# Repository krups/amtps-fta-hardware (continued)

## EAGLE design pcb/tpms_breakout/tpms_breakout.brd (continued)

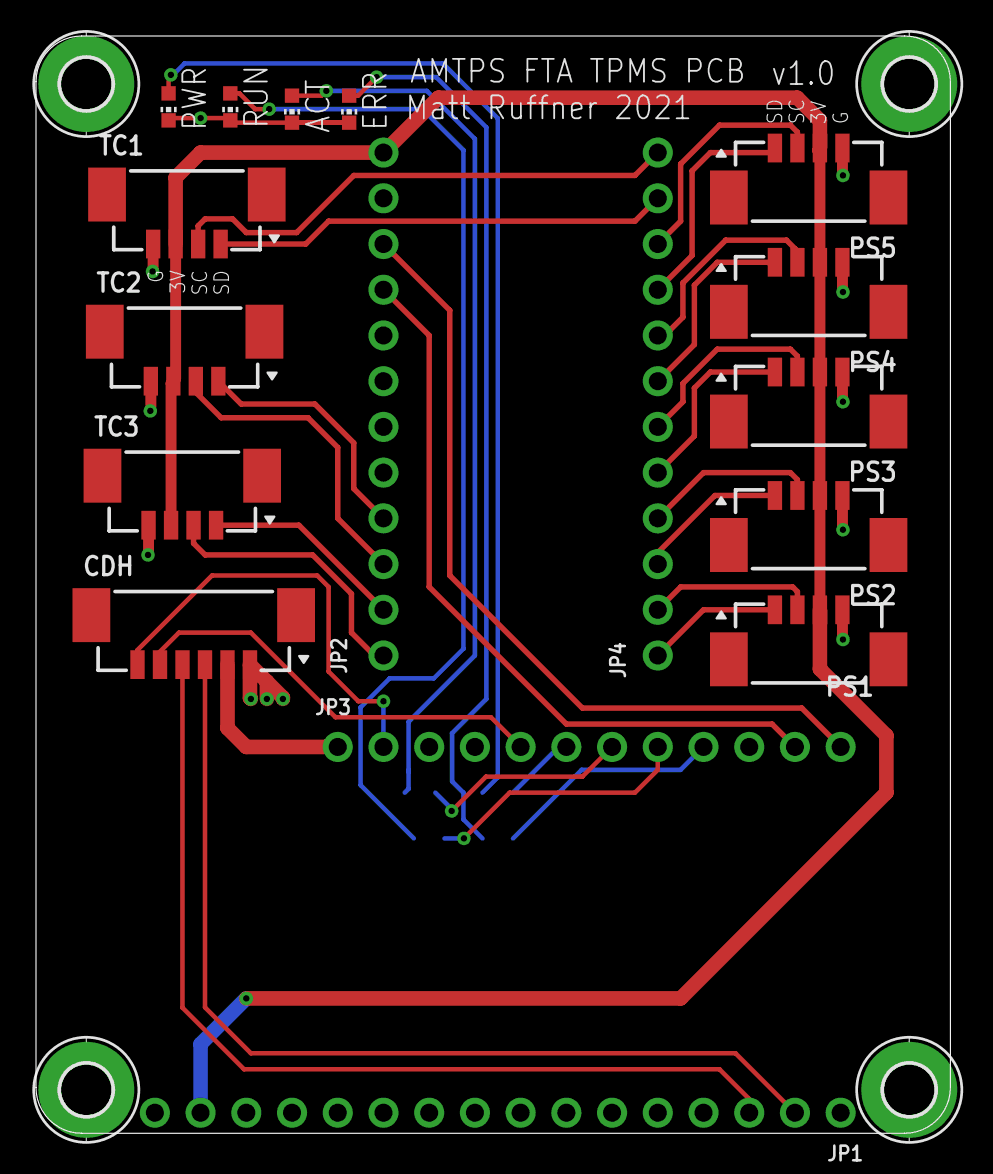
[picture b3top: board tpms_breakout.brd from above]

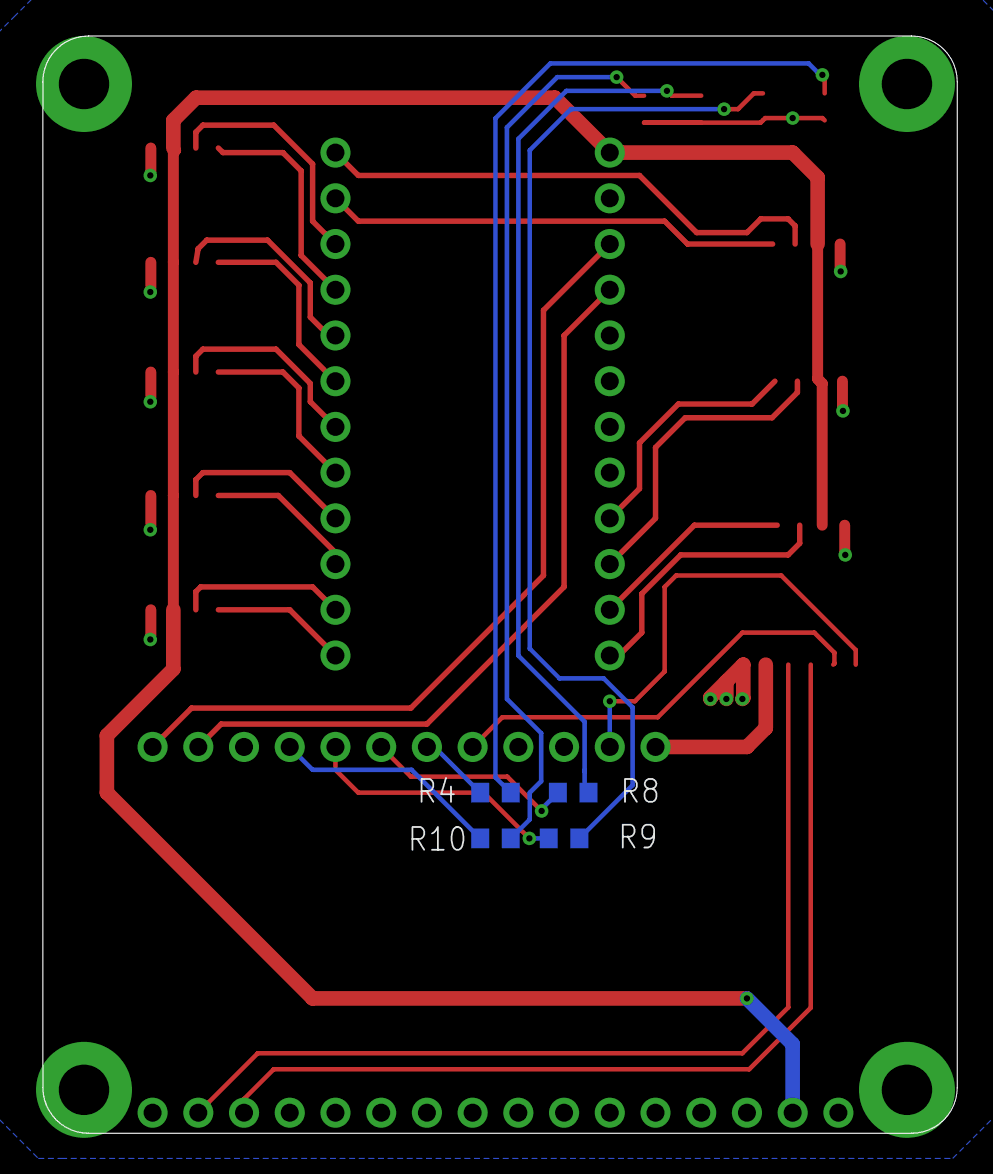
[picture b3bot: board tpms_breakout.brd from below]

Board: 2 copper layers, 50.8 x 61.0 mm, 25 parts (4 on the bottom side), 33 nets.

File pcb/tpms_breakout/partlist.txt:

Partlist

Exported from tpms_breakout.sch at 10/19/21 1:53 PM

EAGLE Version 9.6.2 Copyright (c) 1988-2020 Autodesk, Inc.

Assembly variant: 

Part     Value              Device             Package      Library             Sheet

ACT                         LEDCHIP-LED0603    CHIP-LED0603 adafruit            1
CDH      53398-0610         53398-0610         53398-0610   con-molex-picoblade 1
ERR                         LEDCHIP-LED0603    CHIP-LED0603 adafruit            1
H1       MOUNT-PAD-ROUND2.8 MOUNT-PAD-ROUND2.8 2,8-PAD      holes               1
H2       MOUNT-PAD-ROUND2.8 MOUNT-PAD-ROUND2.8 2,8-PAD      holes               1
H3       MOUNT-PAD-ROUND2.8 MOUNT-PAD-ROUND2.8 2,8-PAD      holes               1
H4       MOUNT-PAD-ROUND2.8 MOUNT-PAD-ROUND2.8 2,8-PAD      holes               1
JP1                         HEADER-1X16ROUND   1X16_ROUND   microbuilder        2
JP2                         HEADER-1X12        1X12_ROUND   microbuilder        2
JP3                         HEADER-1X12        1X12_ROUND   microbuilder        2
JP4                         HEADER-1X12        1X12_ROUND   microbuilder        2
PS1      53398-0410         53398-0410         53398-0410   con-molex-picoblade 1
PS2      53398-0410         53398-0410         53398-0410   con-molex-picoblade 1
PS3      53398-0410         53398-0410         53398-0410   con-molex-picoblade 1
PS4      53398-0410         53398-0410         53398-0410   con-molex-picoblade 1
PS5      53398-0410         53398-0410         53398-0410   con-molex-picoblade 1
PWR                         LEDCHIP-LED0603    CHIP-LED0603 adafruit            1
R4       470                R-US_R0603         R0603        rcl                 1
R8       470                R-US_R0603         R0603        rcl                 1
R9       470                R-US_R0603         R0603        rcl                 1
R10      470                R-US_R0603         R0603        rcl                 1
RUN                         LEDCHIP-LED0603    CHIP-LED0603 adafruit            1
TC1      53398-0410         53398-0410         53398-0410   con-molex-picoblade 1
TC2      53398-0410         53398-0410         53398-0410   con-molex-picoblade 1
TC3      53398-0410         53398-0410         53398-0410   con-molex-picoblade 1

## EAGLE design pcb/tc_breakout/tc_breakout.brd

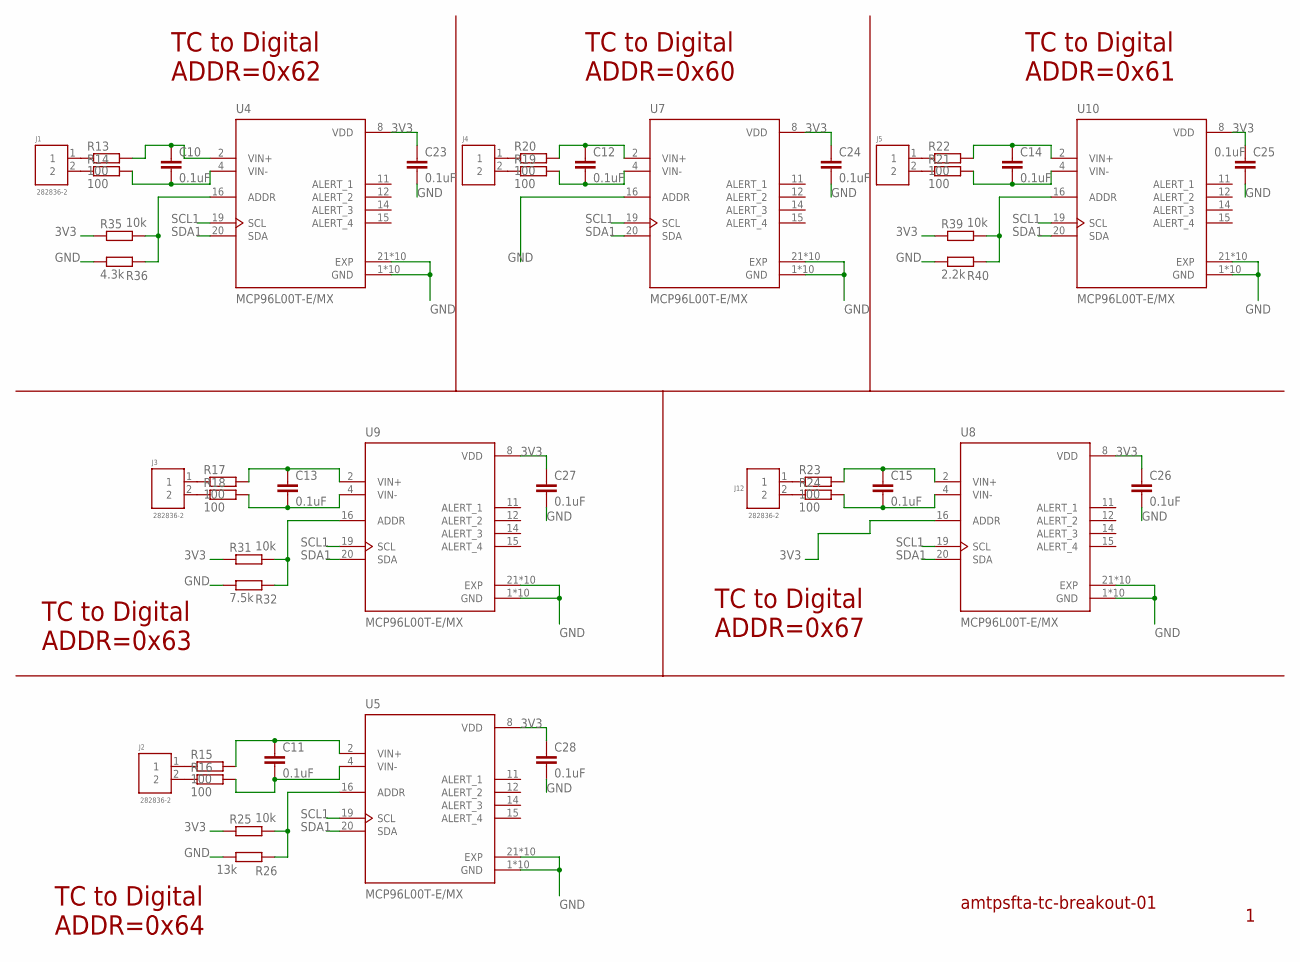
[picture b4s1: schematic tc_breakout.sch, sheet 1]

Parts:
C10, C11, C12, C13, C14, C15, C23, C24, C25, C26, C27, C28: 0.1uF; C0603
J1, J2, J3, J4, J5, J12: 282836-2; CONN_282836-2
R13, R14, R15, R16, R17, R18, R19, R20, R21, R22, R23, R24: 100; R0603
R25, R31, R35, R39: 10k; R0603
R26: 13k; R0603
R32: 7.5k; R0603
R36: 4.3k; R0603
R40: 2.2k; R0603
U4, U5, U7, U8, U9, U10: MCP96L00T-E/MX; QFN65P500X500X100-21N_MCP96L00T-E/MX

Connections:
3V3: C23.1, C24.1, C25.1, C26.1, C27.1, C28.1, R25.1, R31.1, R35.1, R39.1, U4.8 (VDD), U5.8 (VDD), U7.8 (VDD), U8.8 (VDD), U8.16 (ADDR), U9.8 (VDD), U10.8 (VDD); also elsewhere on the board
GND: C23.2, C24.2, C25.2, C26.2, C27.2, C28.2, R26.1, R32.1, R36.1, R40.1, U4.1 (GND), U4.3 (GND), U4.5 (GND), U4.6 (GND), U4.7 (GND), U4.9 (GND), U4.10 (GND), U4.13 (GND), U4.17 (GND), U4.18 (GND), U4.21 (EXP), U4.22 (EXP), U4.23 (EXP), U4.24 (EXP), U4.25 (EXP), U4.26 (EXP), U4.27 (EXP), U4.28 (EXP), U4.29 (EXP), U4.30 (EXP), U5.1 (GND), U5.3 (GND), U5.5 (GND), U5.6 (GND), U5.7 (GND), U5.9 (GND), U5.10 (GND), U5.13 (GND), U5.17 (GND), U5.18 (GND), U5.21 (EXP), U5.22 (EXP), U5.23 (EXP), U5.24 (EXP), U5.25 (EXP), U5.26 (EXP), U5.27 (EXP), U5.28 (EXP), U5.29 (EXP), U5.30 (EXP), U7.1 (GND), U7.3 (GND), U7.5 (GND), U7.6 (GND), U7.7 (GND), U7.9 (GND), U7.10 (GND), U7.13 (GND), U7.16 (ADDR), U7.17 (GND), U7.18 (GND), U7.21 (EXP), U7.22 (EXP), U7.23 (EXP), U7.24 (EXP), U7.25 (EXP), U7.26 (EXP), U7.27 (EXP), U7.28 (EXP), U7.29 (EXP), U7.30 (EXP), U8.1 (GND), U8.3 (GND), U8.5 (GND), U8.6 (GND), U8.7 (GND), U8.9 (GND), U8.10 (GND), U8.13 (GND), U8.17 (GND), U8.18 (GND), U8.21 (EXP), U8.22 (EXP), U8.23 (EXP), U8.24 (EXP), U8.25 (EXP), U8.26 (EXP), U8.27 (EXP), U8.28 (EXP), U8.29 (EXP), U8.30 (EXP), U9.1 (GND), U9.3 (GND), U9.5 (GND), U9.6 (GND), U9.7 (GND), U9.9 (GND), U9.10 (GND), U9.13 (GND), U9.17 (GND), U9.18 (GND), U9.21 (EXP), U9.22 (EXP), U9.23 (EXP), U9.24 (EXP), U9.25 (EXP), U9.26 (EXP), U9.27 (EXP), U9.28 (EXP), U9.29 (EXP), U9.30 (EXP), U10.1 (GND), U10.3 (GND), U10.5 (GND), U10.6 (GND), U10.7 (GND), U10.9 (GND), U10.10 (GND), U10.13 (GND), U10.17 (GND), U10.18 (GND), U10.21 (EXP), U10.22 (EXP), U10.23 (EXP), U10.24 (EXP), U10.25 (EXP), U10.26 (EXP), U10.27 (EXP), U10.28 (EXP), U10.29 (EXP), U10.30 (EXP); also elsewhere on the board
unnamed: J1.1, R13.1
unnamed: J1.2, R14.1
unnamed: J12.1, R23.1
unnamed: C10.1, R13.2, U4.2 (VIN+)
unnamed: C10.2, R14.2, U4.4 (VIN-)
unnamed: J2.1, R15.1
unnamed: J2.2, R16.1
unnamed: J3.1, R17.1
unnamed: J3.2, R18.1
unnamed: J4.2, R19.1
unnamed: J4.1, R20.1
unnamed: J5.2, R21.1
unnamed: J5.1, R22.1
unnamed: J12.2, R24.1
unnamed: C12.1, R20.2, U7.2 (VIN+)
unnamed: C12.2, R19.2, U7.4 (VIN-)
unnamed: C15.1, R23.2, U8.2 (VIN+)
unnamed: C14.2, R21.2, U10.4 (VIN-)
unnamed: C15.2, R24.2, U8.4 (VIN-)
unnamed: C14.1, R22.2, U10.2 (VIN+)
unnamed: C13.1, R17.2, U9.2 (VIN+)
unnamed: C13.2, R18.2, U9.4 (VIN-)
unnamed: C11.1, R15.2, U5.2 (VIN+)
unnamed: C11.2, R16.2, U5.4 (VIN-)
unnamed: R25.2, R26.2, U5.16 (ADDR)
unnamed: R31.2, R32.2, U9.16 (ADDR)
unnamed: R35.2, R36.2, U4.16 (ADDR)
unnamed: R39.2, R40.2, U10.16 (ADDR)
SCL1: U4.19 (SCL), U5.19 (SCL), U7.19 (SCL), U8.19 (SCL), U9.19 (SCL), U10.19 (SCL); also elsewhere on the board
SDA1: U4.20 (SDA), U5.20 (SDA), U7.20 (SDA), U8.20 (SDA), U9.20 (SDA), U10.20 (SDA); also elsewhere on the board

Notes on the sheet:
TC to Digital ADDR=0x60
TC to Digital ADDR=0x61
TC to Digital ADDR=0x62
TC to Digital ADDR=0x67
TC to Digital ADDR=0x63
TC to Digital ADDR=0x64
amtpsfta-tc-breakout-01

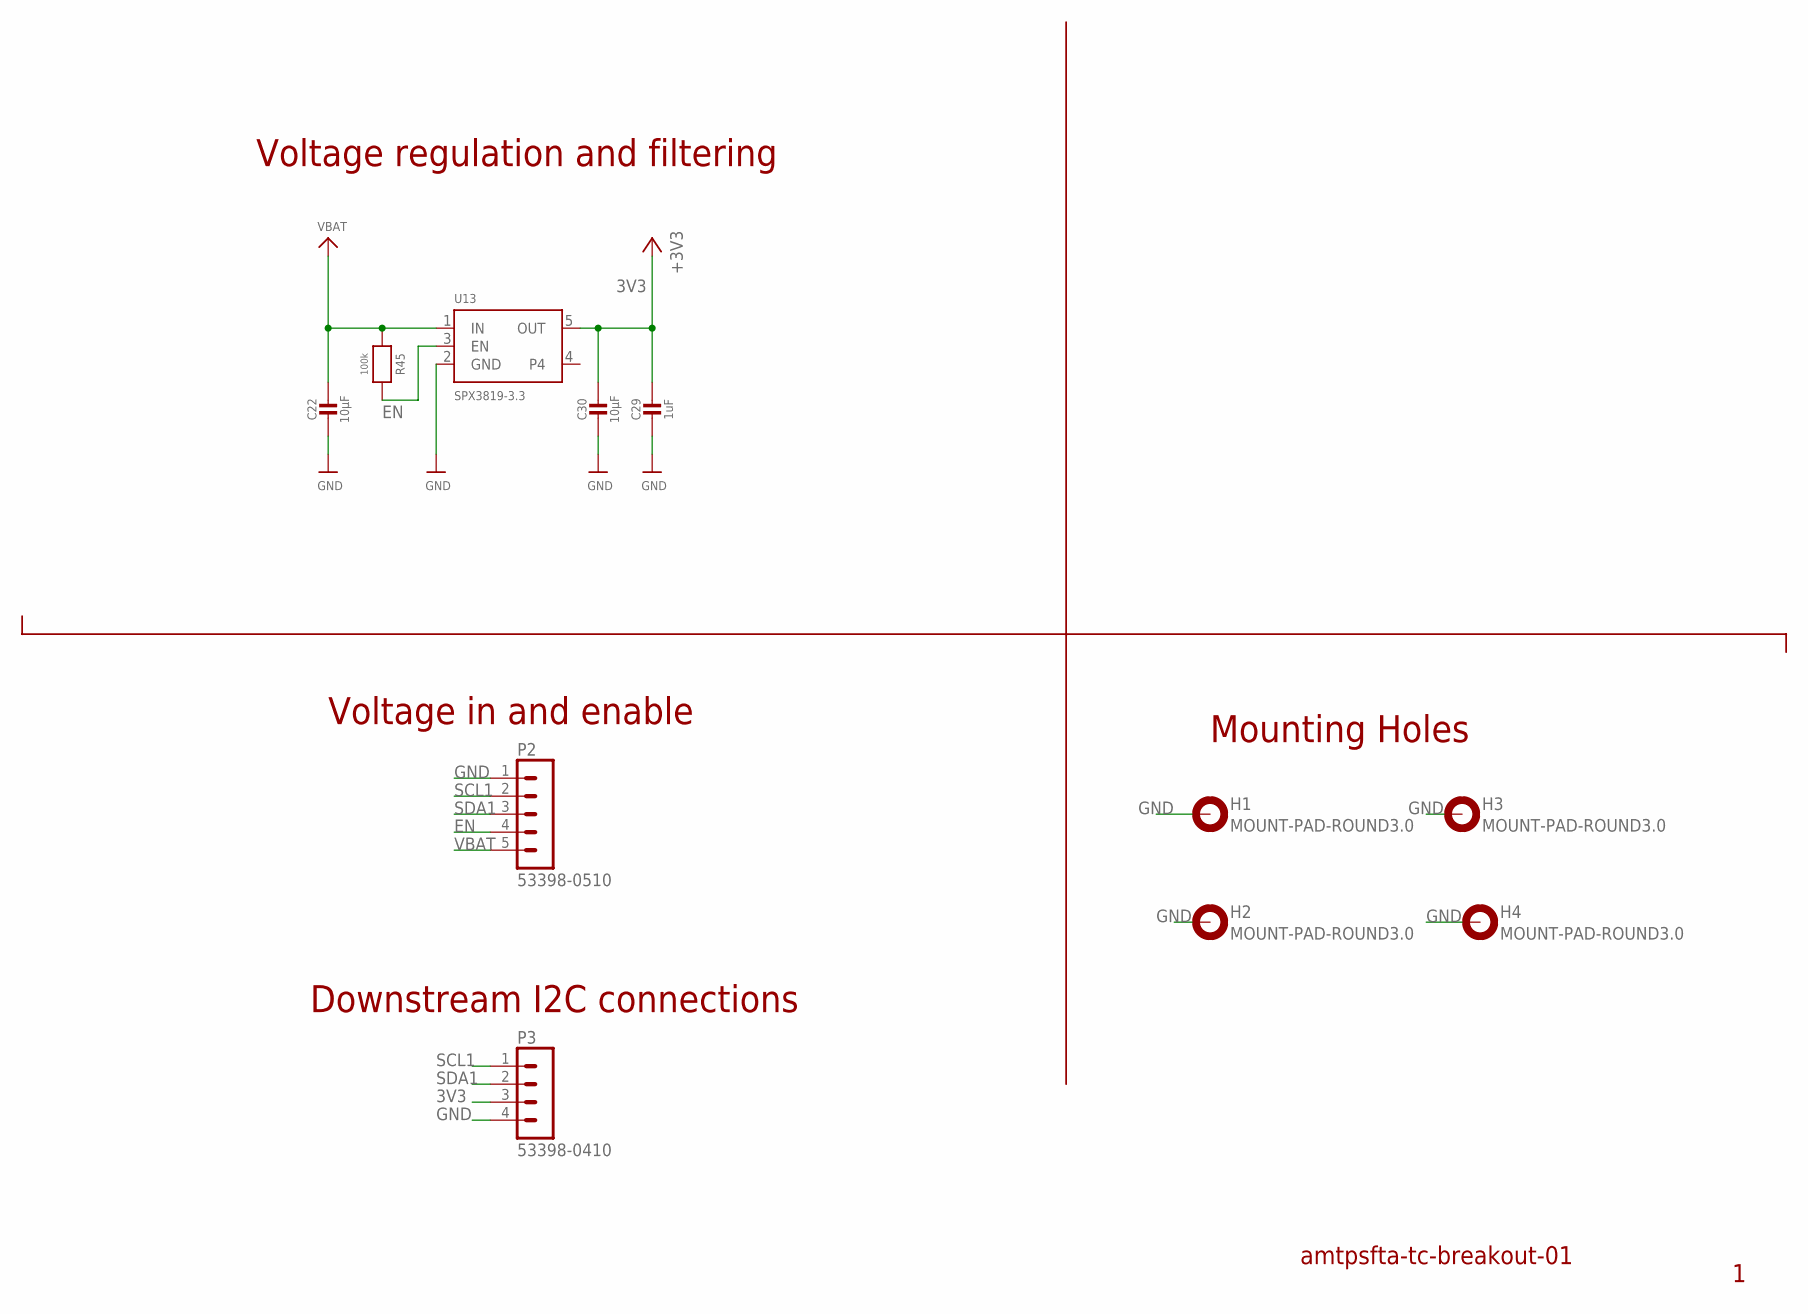
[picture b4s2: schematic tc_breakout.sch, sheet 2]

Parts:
C22, C30: 10µF; 0805-NO
C29: 1uF; 0603-NO
H1, H2, H3, H4: MOUNT-PAD-ROUND3.0; 3,0-PAD
P2: 53398-0510
P3: 53398-0410
R45: 100k; 0603-NO
U13: SPX3819-3.3; SOT23-5

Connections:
3V3: C29.1, C30.1, P3.3, U13.5 (OUT); also elsewhere on the board
EN: P2.4, R45.2, U13.3 (EN)
GND: C22.2, C29.2, C30.2, H1.B3,0, H2.B3,0, H3.B3,0, H4.B3,0, P2.1, P3.4, U13.2 (GND); also elsewhere on the board
SCL1: P2.2, P3.1; also elsewhere on the board
SDA1: P2.3, P3.2; also elsewhere on the board
VBAT: C22.1, P2.5, R45.1, U13.1 (IN)

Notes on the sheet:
Mounting Holes
Voltage in and enable
Downstream I2C connections
Voltage regulation and filtering
amtpsfta-tc-breakout-01

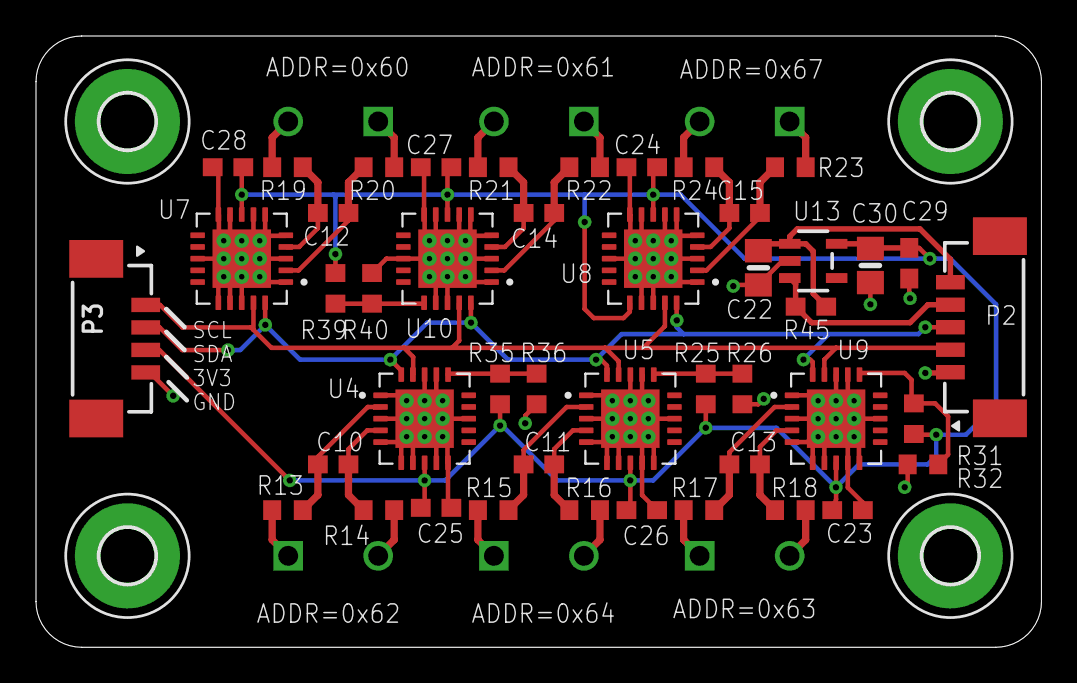
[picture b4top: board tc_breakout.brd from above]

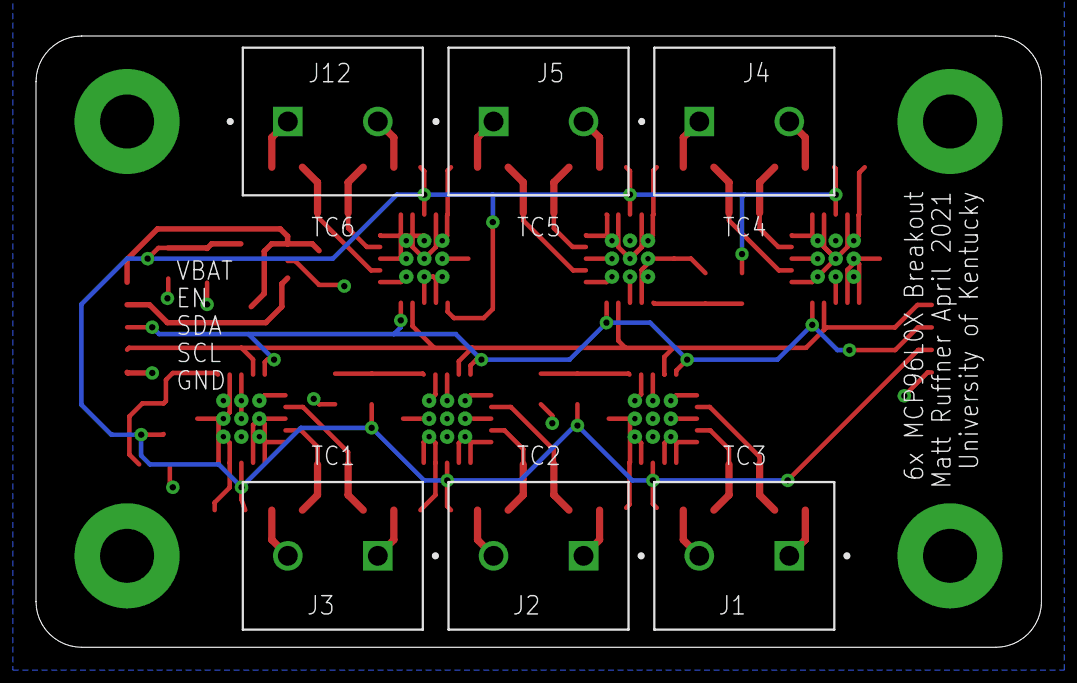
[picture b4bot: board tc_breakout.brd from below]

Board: 2 copper layers, 55.9 x 34.0 mm, 55 parts (6 on the bottom side), 34 nets.

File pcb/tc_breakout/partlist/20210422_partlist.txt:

Partlist

Exported from tc_breakout.brd at 4/22/21 8:15 AM

EAGLE Version 9.6.2 Copyright (c) 1988-2020 Autodesk, Inc.

Assembly variant: 

Part     Value              Package                              Library             Position (mil)        Orientation

C10      0.1uF              C0603                                rcl                 (650 400)             R0
C11      0.1uF              C0603                                rcl                 (1100 400)            R0
C12      0.1uF              C0603                                rcl                 (650 950)             R180
C13      0.1uF              C0603                                rcl                 (1550 400)            R0
C14      0.1uF              C0603                                rcl                 (1100 950)            R180
C15      0.1uF              C0603                                rcl                 (1550 950)            R180
C22      10µF               0805-NO                              microbuilder        (1580 830)            R270
C23      0.1uF              C0603                                rcl                 (1775 300)            R0
C24      0.1uF              C0603                                rcl                 (1325 1050)           R180
C25      0.1uF              C0603                                rcl                 (875 305)             R0
C26      0.1uF              C0603                                rcl                 (1325 300)            R0
C27      0.1uF              C0603                                rcl                 (875 1050)            R180
C28      0.1uF              C0603                                rcl                 (420 1050)            R180
C29      1uF                0603-NO                              microbuilder        (1910 840)            R270
C30      10µF               0805-NO                              microbuilder        (1825 835)            R270
H1       MOUNT-PAD-ROUND3.0 3,0-PAD                              holes               (200 200)             R0
H2       MOUNT-PAD-ROUND3.0 3,0-PAD                              holes               (2000 200)            R0
H3       MOUNT-PAD-ROUND3.0 3,0-PAD                              holes               (200 1150)            R0
H4       MOUNT-PAD-ROUND3.0 3,0-PAD                              holes               (2000 1150)           R0
J1       282836-2           CONN_282836-2                        282836-2            (650 200)             MR180
J2       282836-2           CONN_282836-2                        282836-2            (1100 200)            MR180
J3       282836-2           CONN_282836-2                        282836-2            (1550 200)            MR180
J4       282836-2           CONN_282836-2                        282836-2            (650 1150)            MR0
J5       282836-2           CONN_282836-2                        282836-2            (1100 1150)           MR0
J12      282836-2           CONN_282836-2                        282836-2            (1550 1150)           MR0
P2       53398-0510         53398-0510                           con-molex-picoblade (2000 700)            R270
R13      100                R0603                                rcl                 (550 300)             R0
R14      100                R0603                                rcl                 (750 300)             R180
R15      100                R0603                                rcl                 (1000 300)            R0
R16      100                R0603                                rcl                 (1200 300)            R180
R17      100                R0603                                rcl                 (1450 300)            R0
R18      100                R0603                                rcl                 (1650 300)            R180
R19      100                R0603                                rcl                 (550 1050)            R0
R20      100                R0603                                rcl                 (750 1050)            R180
R21      100                R0603                                rcl                 (1000 1050)           R0
R22      100                R0603                                rcl                 (1200 1050)           R180
R23      100                R0603                                rcl                 (1650 1050)           R180
R24      100                R0603                                rcl                 (1450 1050)           R0
R25      10k                R0603                                rcl                 (1465 565)            R90
R26      7.87k              R0603                                rcl                 (1545 565)            R90
R31      10k                R0603                                rcl                 (1920 500)            R90
R32      4.3k               R0603                                rcl                 (1940 400)            R0
R35      10k                R0603                                rcl                 (1015 565)            R90
R36      4.3k               R0603                                rcl                 (1095 565)            R90
R39      10k                R0603                                rcl                 (655 785)             R270
R40      2.2k               R0603                                rcl                 (735 785)             R270
R45      100k               0603-NO                              microbuilder        (1695 745)            R180
U4       MCP96L00T-E/MX     QFN65P500X500X100-21N_MCP96L00T-E/MX MCP96L00T-E_MX      (850 500)             R0
U5       MCP96L00T-E/MX     QFN65P500X500X100-21N_MCP96L00T-E/MX MCP96L00T-E_MX      (1300 500)            R0
U7       MCP96L00T-E/MX     QFN65P500X500X100-21N_MCP96L00T-E/MX MCP96L00T-E_MX      (450 850)             R180
U8       MCP96L00T-E/MX     QFN65P500X500X100-21N_MCP96L00T-E/MX MCP96L00T-E_MX      (1350 850)            R180
U9       MCP96L00T-E/MX     QFN65P500X500X100-21N_MCP96L00T-E/MX MCP96L00T-E_MX      (1750 500)            R0
U10      MCP96L00T-E/MX     QFN65P500X500X100-21N_MCP96L00T-E/MX MCP96L00T-E_MX      (900 850)             R180
U13      SPX3819-3.3        SOT23-5                              microbuilder        (1700 845)            R270

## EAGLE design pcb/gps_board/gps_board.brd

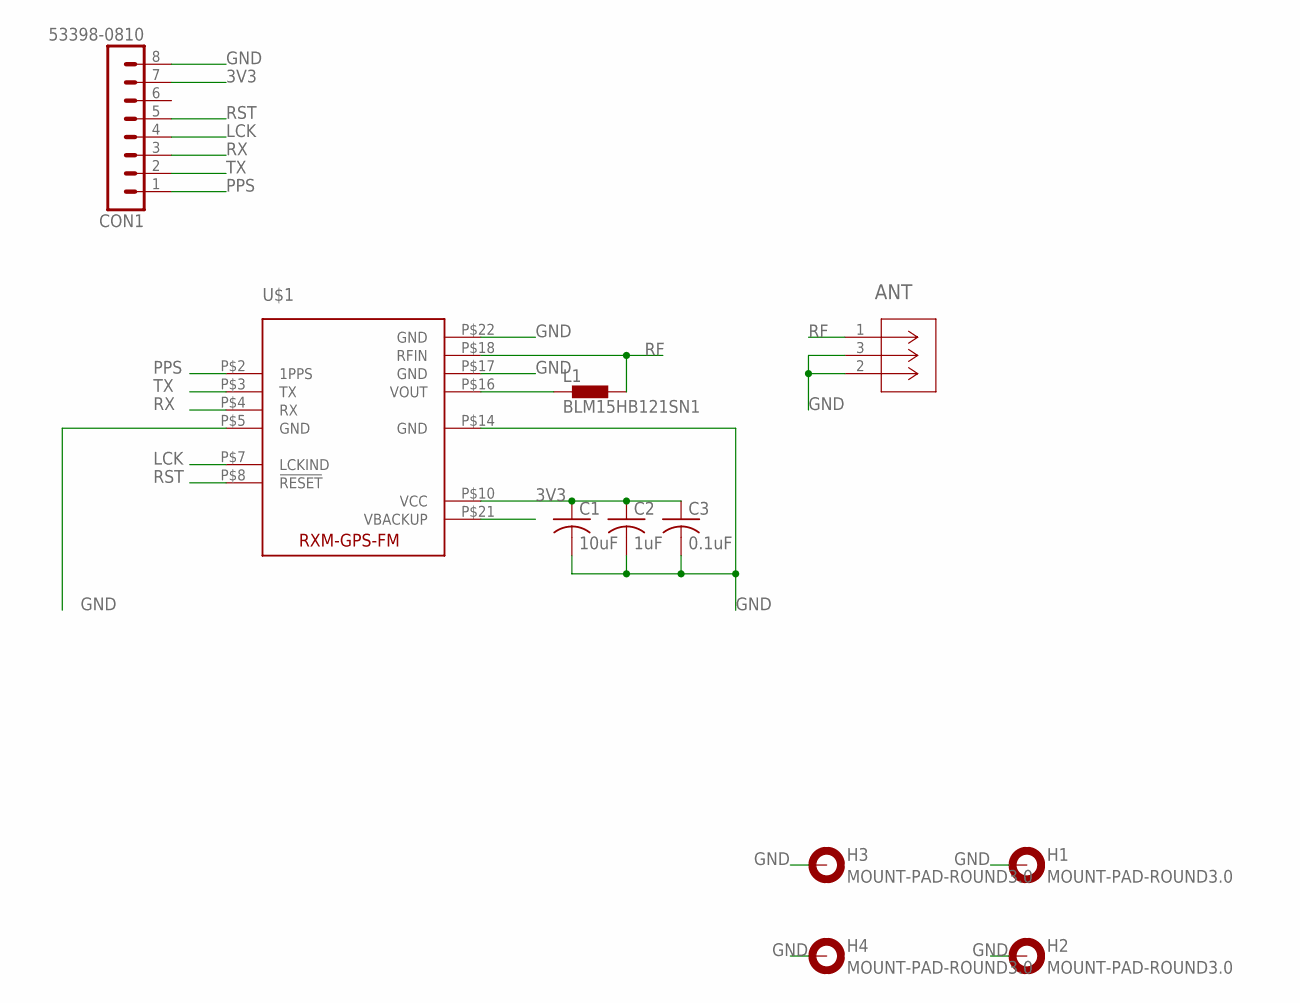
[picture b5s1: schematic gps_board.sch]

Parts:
ANT: U.FL-R-SMT-1(10); CONN_R-SMT-1(10)
C1: 10uF; C0603
C2: 1uF; C0603
C3: 0.1uF; C0603
CON1: 53398-0810
H1, H2, H3, H4: MOUNT-PAD-ROUND3.0; 3,0-PAD
L1: BLM15HB121SN1; 0402
U$1: RXM-GPS-FM

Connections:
3V3: C1.1, C2.1, C3.1, CON1.7, U$1.P$10 (VCC)
GND: ANT.2, ANT.3, C1.2, C2.2, C3.2, CON1.8, H1.B3,0, H2.B3,0, H3.B3,0, H4.B3,0, U$1.P$5 (GND), U$1.P$14 (GND), U$1.P$17 (GND), U$1.P$22 (GND)
LCK: CON1.4, U$1.P$7 (LCKIND)
unnamed: L1.1, U$1.P$16 (VOUT)
PPS: CON1.1, U$1.P$2 (1PPS)
RF: ANT.1, L1.2, U$1.P$18 (RFIN)
RST: CON1.5, U$1.P$8 (!RESET)
RX: CON1.3, U$1.P$4 (RX)
TX: CON1.2, U$1.P$3 (TX)

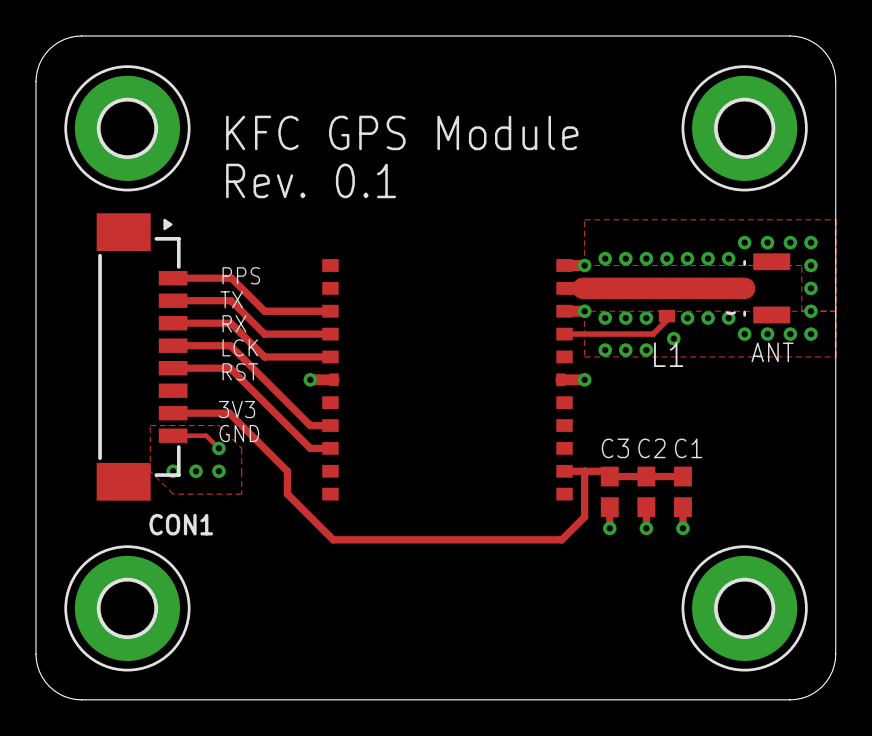
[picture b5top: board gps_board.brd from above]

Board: 2 copper layers, 44.4 x 36.9 mm, 11 parts (0 on the bottom side), 9 nets.

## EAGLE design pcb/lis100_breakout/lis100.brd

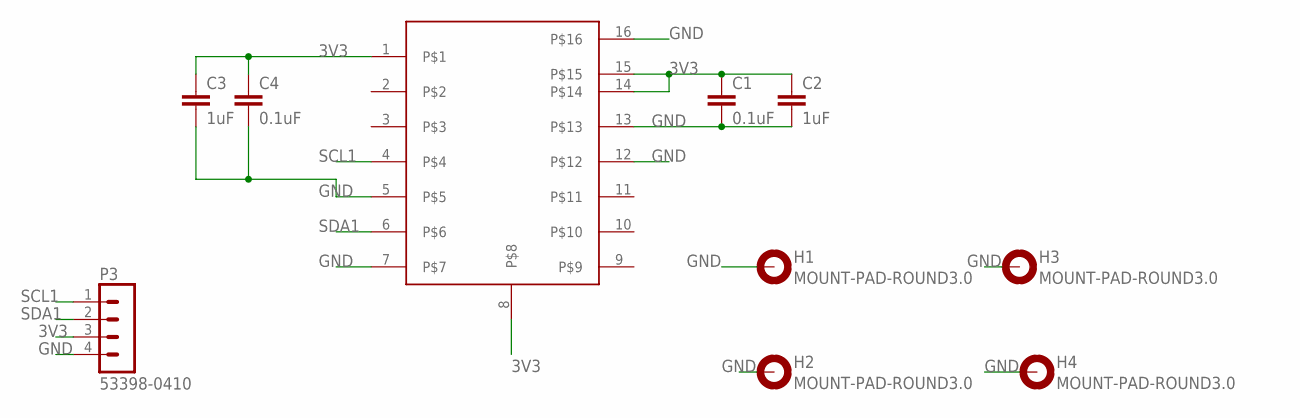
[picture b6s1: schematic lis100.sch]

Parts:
C1, C4: 0.1uF; C0603
C2, C3: 1uF; C0603
H1, H2, H3, H4: MOUNT-PAD-ROUND3.0; 3,0-PAD
P3: 53398-0410
U$1: H3LIS100DL; XDCR_LIS3DHTR

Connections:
3V3: C1.1, C2.1, C3.1, C4.1, P3.3, U$1.1, U$1.8, U$1.14, U$1.15
GND: C1.2, C2.2, C3.2, C4.2, H1.B3,0, H2.B3,0, H3.B3,0, H4.B3,0, P3.4, U$1.5, U$1.7, U$1.12, U$1.13, U$1.16
SCL1: P3.1, U$1.4
SDA1: P3.2, U$1.6

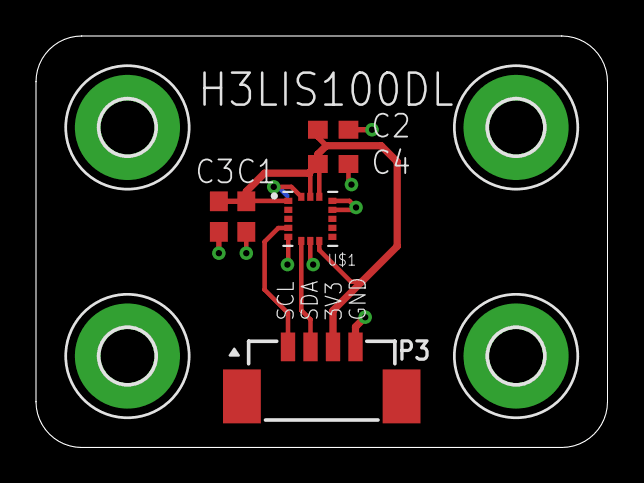
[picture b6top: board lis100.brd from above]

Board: 2 copper layers, 31.8 x 22.9 mm, 10 parts (0 on the bottom side), 4 nets.

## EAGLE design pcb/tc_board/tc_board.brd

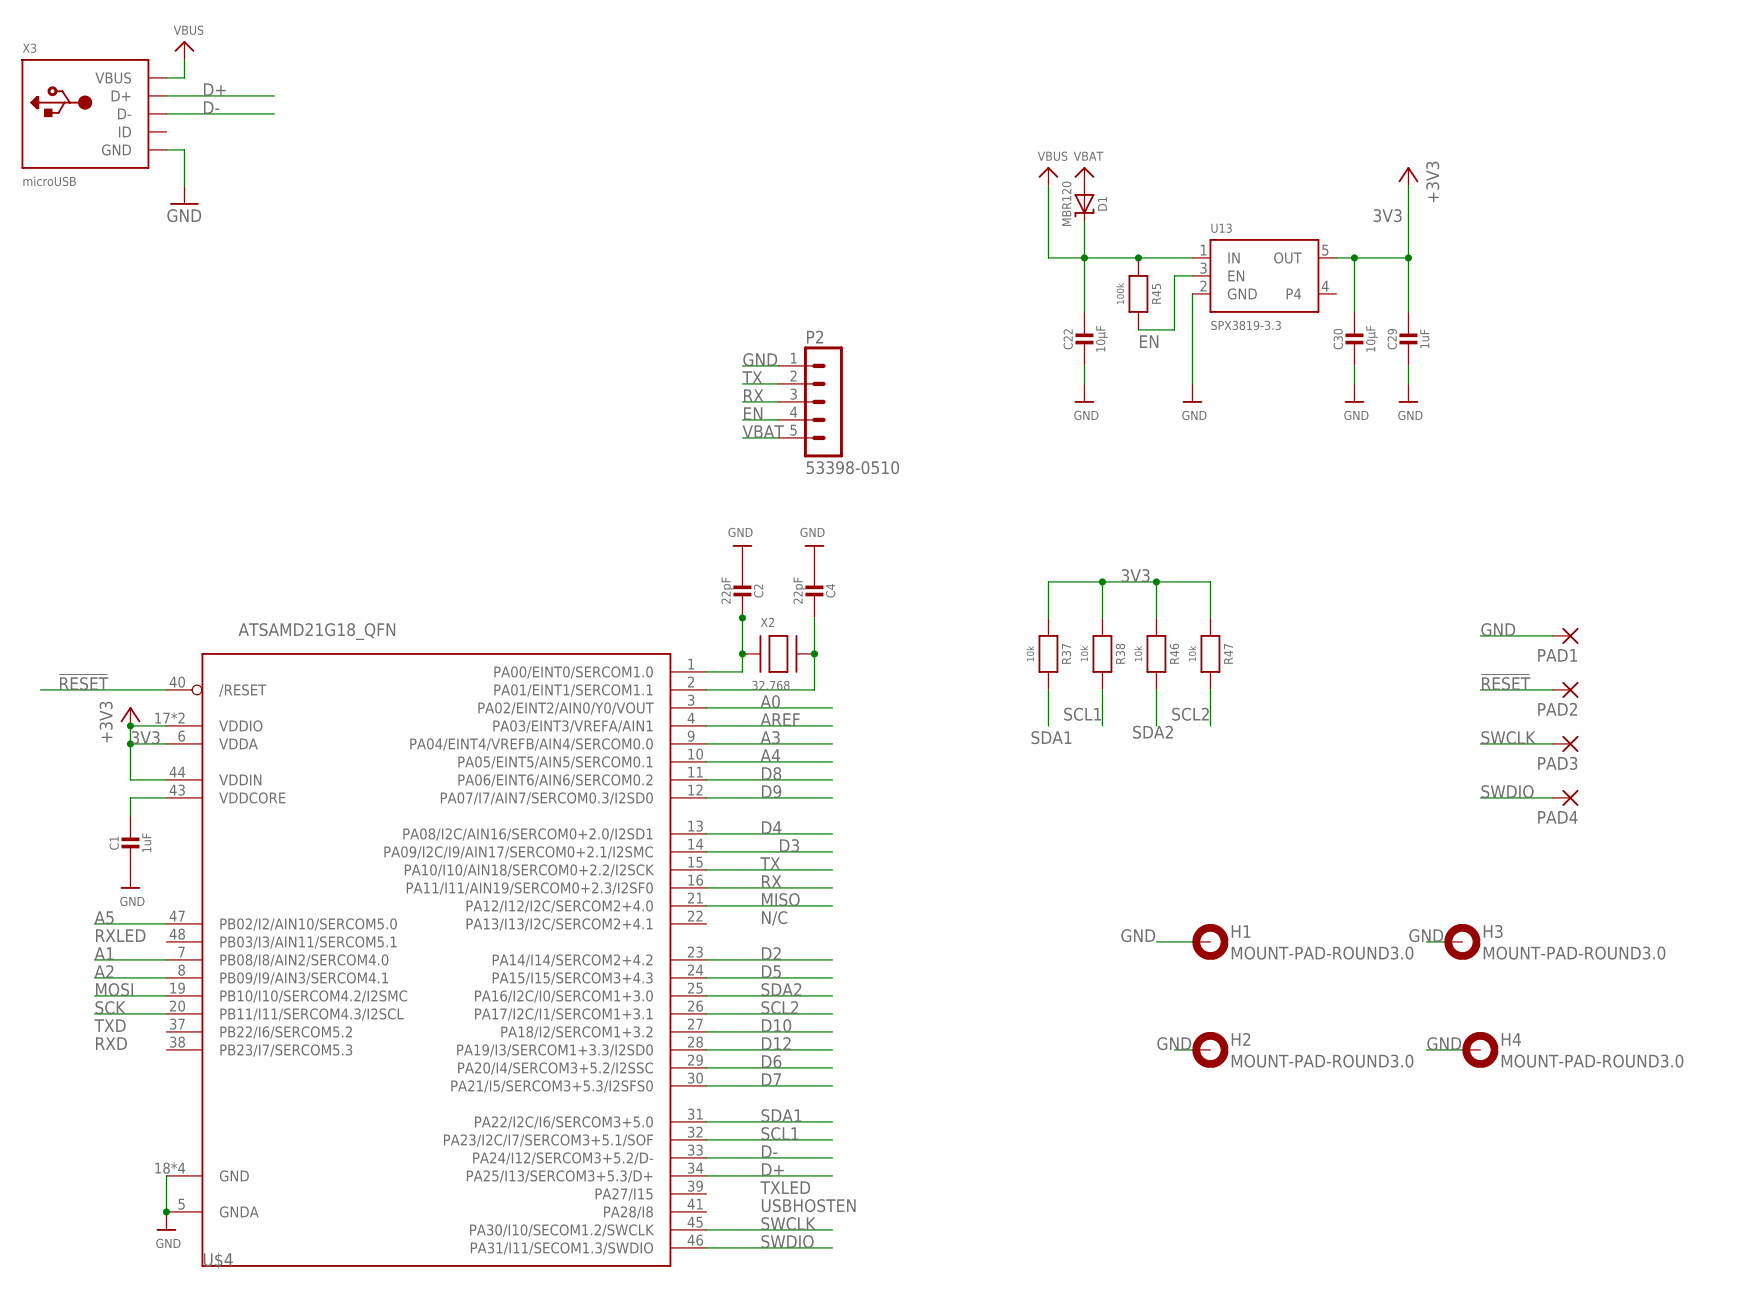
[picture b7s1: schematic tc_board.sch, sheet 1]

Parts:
C1, C29: 1uF; 0603-NO
C2, C4: 22pF; 0603-NO
C22, C30: 10µF; 0805-NO
D1: MBR120; SOD-123
H1, H2, H3, H4: MOUNT-PAD-ROUND3.0; 3,0-PAD
P2: 53398-0510
PAD1, PAD2, PAD3, PAD4: SMD2; SMD1,27-2,54
R37, R38, R46, R47: 10k; 0603-NO
R45: 100k; 0603-NO
U13: SPX3819-3.3; SOT23-5
U$4: ATSAMD21G18_QFN; TQFN48_7MM
X2: 32.768; XTAL3215
X3: microUSB; 4UCONN_20329_V2

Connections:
3V3: C29.1, C30.1, R37.1, R38.1, R46.1, R47.1, U13.5 (OUT), U$4.6 (VDDA), U$4.17 (VDDIO), U$4.36 (VDDIO), U$4.44 (VDDIN); also elsewhere on the board
!RESET: PAD2.1, U$4.40 (/RESET)
A0: U$4.3 (PA02/EINT2/AIN0/Y0/VOUT)
A1: U$4.7 (PB08/I8/AIN2/SERCOM4.0)
A2: U$4.8 (PB09/I9/AIN3/SERCOM4.1)
A3: U$4.9 (PA04/EINT4/VREFB/AIN4/SERCOM0.0)
A4: U$4.10 (PA05/EINT5/AIN5/SERCOM0.1)
A5: U$4.47 (PB02/I2/AIN10/SERCOM5.0)
AREF: U$4.4 (PA03/EINT3/VREFA/AIN1)
D2: U$4.23 (PA14/I14/SERCOM2+4.2)
D3: U$4.14 (PA09/I2C/I9/AIN17/SERCOM0+2.1/I2SMC)
D4: U$4.13 (PA08/I2C/AIN16/SERCOM0+2.0/I2SD1)
D5: U$4.24 (PA15/I15/SERCOM3+4.3)
D6: U$4.29 (PA20/I4/SERCOM3+5.2/I2SSC)
D7: U$4.30 (PA21/I5/SERCOM3+5.3/I2SFS0)
D8: U$4.11 (PA06/EINT6/AIN6/SERCOM0.2)
D9: U$4.12 (PA07/I7/AIN7/SERCOM0.3/I2SD0)
D10: U$4.27 (PA18/I2/SERCOM1+3.2)
D12: U$4.28 (PA19/I3/SERCOM1+3.3/I2SD0)
D+: U$4.34 (PA25/I13/SERCOM3+5.3/D+), X3.D+
D-: U$4.33 (PA24/I12/SERCOM3+5.2/D-), X3.D-
EN: P2.4, R45.2, U13.3 (EN)
GND: C1.2, C2.2, C4.2, C22.2, C29.2, C30.2, H1.B3,0, H2.B3,0, H3.B3,0, H4.B3,0, P2.1, PAD1.1, U13.2 (GND), U$4.5 (GNDA), U$4.18 (GND), U$4.35 (GND), U$4.42 (GND), U$4.THERMAL (GND), X3.BASE@1 (GND), X3.BASE@2 (GND), X3.GND, X3.SPRT@1 (GND), X3.SPRT@2 (GND), X3.SPRT@3 (GND), X3.SPRT@4 (GND); also elsewhere on the board
MISO: U$4.21 (PA12/I12/I2C/SERCOM2+4.0)
MOSI: U$4.19 (PB10/I10/SERCOM4.2/I2SMC)
unnamed: C2.1, U$4.1 (PA00/EINT0/SERCOM1.0), X2.P$1
unnamed: C4.1, U$4.2 (PA01/EINT1/SERCOM1.1), X2.P$2
RX: P2.3, U$4.16 (PA11/I11/AIN19/SERCOM0+2.3/I2SF0)
SCK: U$4.20 (PB11/I11/SERCOM4.3/I2SCL)
SCL1: R38.2, U$4.32 (PA23/I2C/I7/SERCOM3+5.1/SOF); also elsewhere on the board
SCL2: R47.2, U$4.26 (PA17/I2C/I1/SERCOM1+3.1); also elsewhere on the board
SDA1: R37.2, U$4.31 (PA22/I2C/I6/SERCOM3+5.0); also elsewhere on the board
SDA2: R46.2, U$4.25 (PA16/I2C/I0/SERCOM1+3.0); also elsewhere on the board
SWCLK: PAD3.1, U$4.45 (PA30/I10/SECOM1.2/SWCLK)
SWDIO: PAD4.1, U$4.46 (PA31/I11/SECOM1.3/SWDIO)
TX: P2.2, U$4.15 (PA10/I10/AIN18/SERCOM0+2.2/I2SCK)
VBAT: D1.A, P2.5
VBUS: C22.1, D1.C, R45.1, U13.1 (IN), X3.VBUS
VDDCORE: C1.1, U$4.43 (VDDCORE)

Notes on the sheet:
N/C
TXLED
USBHOSTEN
RXLED
TXD
RXD
